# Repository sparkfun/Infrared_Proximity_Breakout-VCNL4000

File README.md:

**NOTE:** *This product has been retired from our catalog. If you are looking for more up-to-date info, please check out some of these resources to see how other users are still hacking and improving on this product.*
* *[SparkFun Forum](https://forum.sparkfun.com/)*
* *[Comments Here on GitHub](https://github.com/sparkfun/Infrared_Proximity_Breakout-VCNL4000/issues)*

SparkFun Infrared Proximity Breakout - VCNL4000
========================================

[*SparkFun Infrared Proximity Breakout - VCNL4000 (BOB-10901)*](https://www.sparkfun.com/products/10901)

The VCNL4000 can detect its proximity to an object using IR within a range of about 20cm. 
Proximity data as well as ambient light level data can be collected over an I2C interface.

Repository Contents
-------------------

* **/Firmware** - Example Arduino code 
* **/Hardware** - Eagle design files (.brd, .sch)
* **/Production** - Production panel files (.brd)

Documentation
--------------
* **[SparkFun Fritzing repo](https://github.com/sparkfun/Fritzing_Parts)** - Fritzing diagrams for SparkFun products.
* **[SparkFun 3D Model repo](https://github.com/sparkfun/3D_Models)** - 3D models of SparkFun products. 

License Information
-------------------
This product is _**open source**_! 

The **hardware** is released under [Creative Commons ShareAlike 4.0 International](https://creativecommons.org/licenses/by-sa/4.0/).

The **code** is beerware; if you see me (or any other SparkFun employee) at the local, and you've found our code helpful, please buy us a round!

Please use, reuse, and modify these files as you see fit. Please maintain attribution to SparkFun Electronics and release anything derivative under the same license.

Distributed as-is; no warranty is given.

- Your friends at SparkFun.

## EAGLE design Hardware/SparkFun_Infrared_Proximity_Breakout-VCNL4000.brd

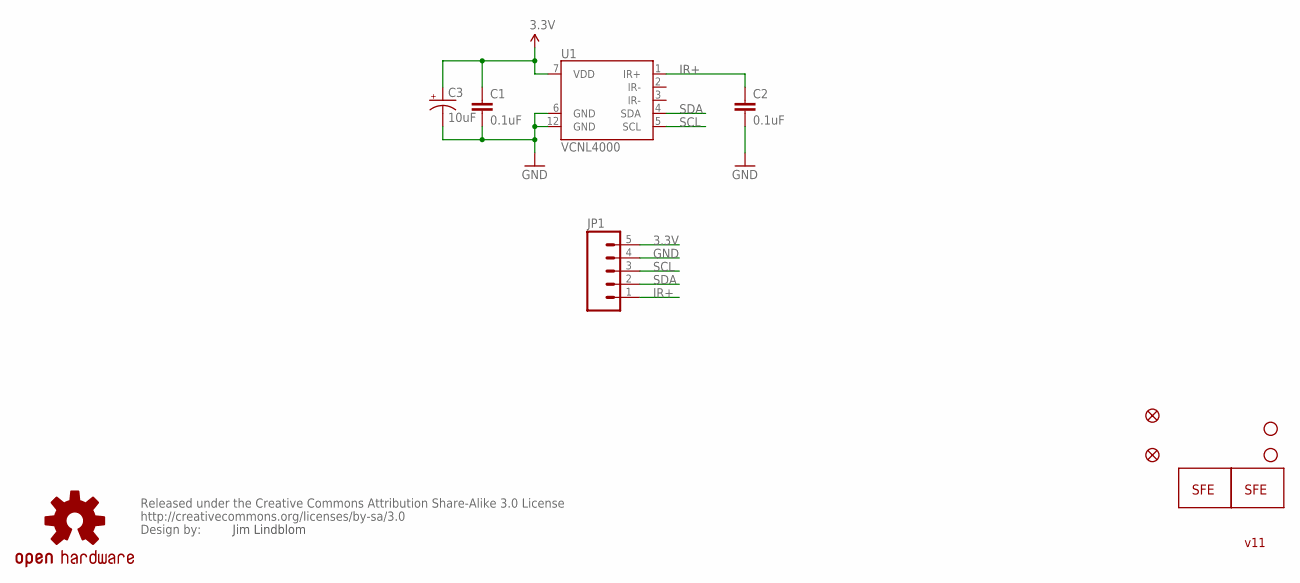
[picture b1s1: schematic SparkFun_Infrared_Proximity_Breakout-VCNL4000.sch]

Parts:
C1, C2: 0.1uF; 0402-CAP
C3: 10uF; EIA3216
JP1: M05PTH; 1X05
JP2: LOGO-SFENW2; SFE-NEW-WEB
JP3, JP4: STAND-OFF
JP5: LOGO-SFESK; SFE-LOGO-FLAME
JP6, JP7: FIDUCIALUFIDUCIAL; MICRO-FIDUCIAL
U1: VCNL4000
U$1: OSHW-LOGOS; OSHW-LOGO-S
U$2: CREATIVE_COMMONS

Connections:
3.3V: C1.1, C3.A (+), JP1.5, U1.7 (VDD)
GND: C1.2, C2.2, C3.C (-), JP1.4, U1.6 (GND), U1.12 (GND)
IR+: C2.1, JP1.1, U1.1 (IR+)
SCL: JP1.3, U1.5 (SCL)
SDA: JP1.2, U1.4 (SDA)

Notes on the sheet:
Jim Lindblom
v11

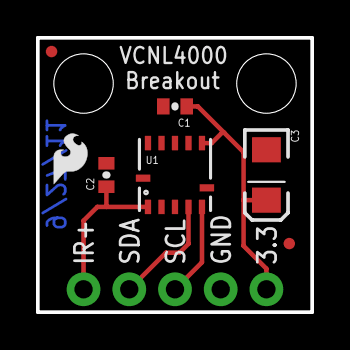
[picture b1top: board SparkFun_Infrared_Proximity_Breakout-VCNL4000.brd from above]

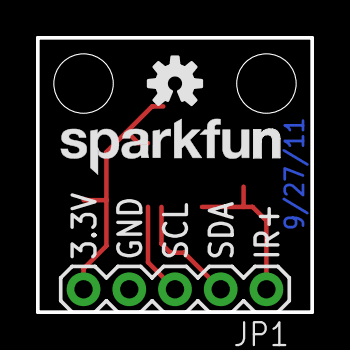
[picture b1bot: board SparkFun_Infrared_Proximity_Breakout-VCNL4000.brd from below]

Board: 2 copper layers, 15.2 x 15.2 mm, 13 parts (3 on the bottom side), 5 nets.

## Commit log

2015-05-05 Adding hardware
2015-05-05 Updating example sketch README
2020-05-22 Update SparkFunVCNL4000Example.ino
    Removing line [based on feedback](https://github.com/sparkfun/Infrared_Proximity_Breakout-VCNL4000/issues/1).

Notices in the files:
parts and their libraries:
SparkFun: Released under the Creative Commons Attribution Share-Alike 3.0 License
SparkFun: http://creativecommons.org/licenses/by-sa/3.0
